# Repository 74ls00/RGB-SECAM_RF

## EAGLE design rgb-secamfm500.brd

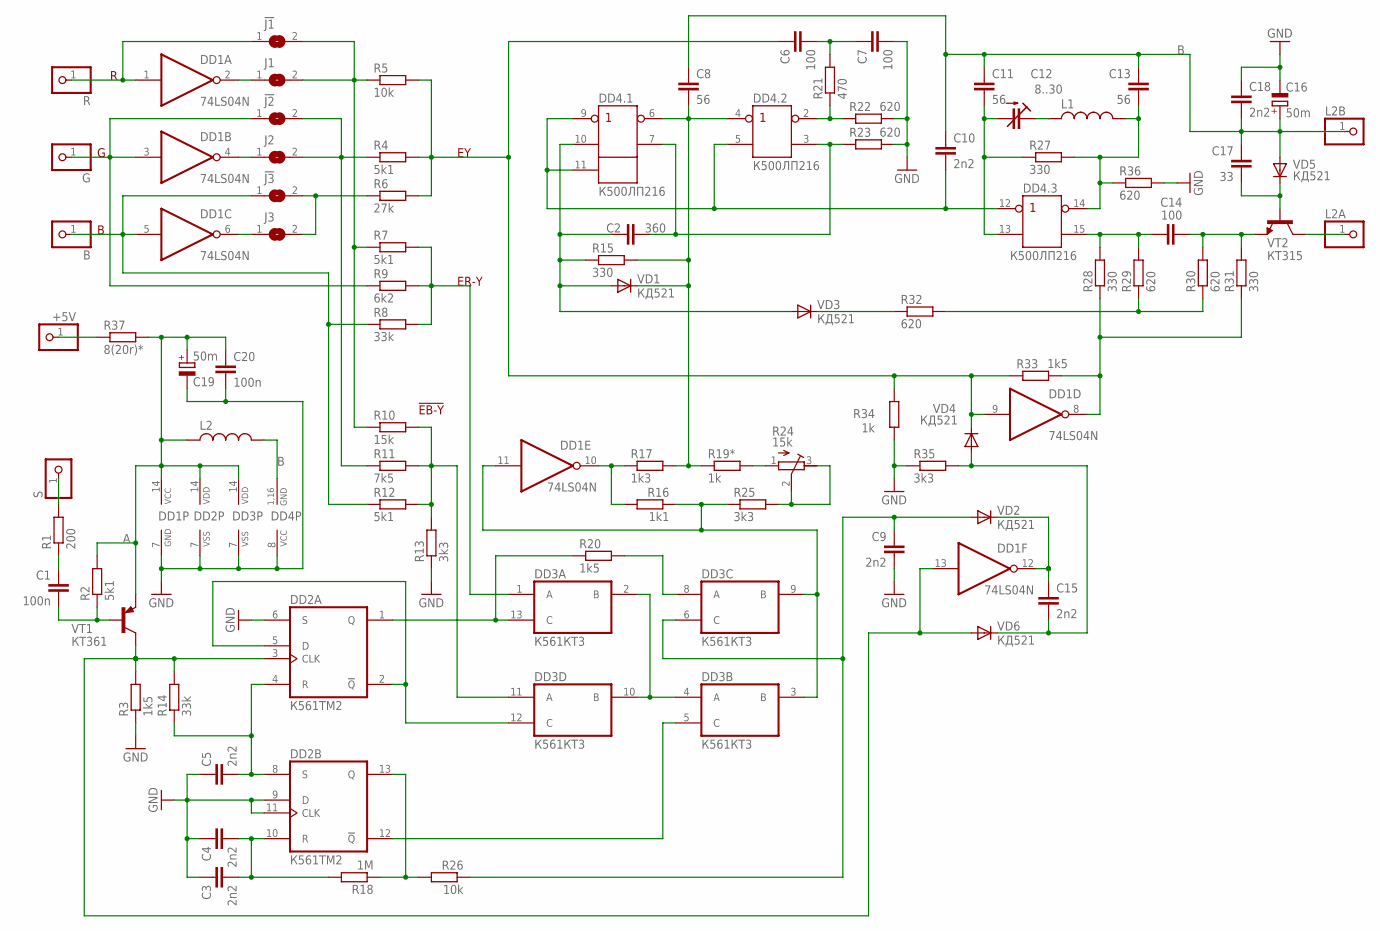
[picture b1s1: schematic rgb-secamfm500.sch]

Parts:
!J1, !J2, !J3: SJ
+5V: PINHD-1X1; 1X01
B: PINHD-1X1; 1X01
C1: 100n; C025-025X050
C2: 360; C0805K
C3, C4: 2n2; C0805
C5, C9, C10, C15, C18: 2n2; C0805K
C6, C7, C14: 100; C0805K
C8, C11, C13: 56; C0805K
C12: 8..30; CTRIM808-1
C16, C19: 50m; E2,5-6
C17: 33; C0805K
C20: 100n; C0805K
DD1: 74LS04N; DIL14
DD2: К561ТМ2; DIL14
DD3: К561КТ3; DIL14
DD4: К500ЛП216; DIL16B
G: PINHD-1X1; 1X01
J1, J2, J3: SJ
L1: L1
L2: L-US0204/5; 0204/5
L2A, L2B: PINHD-1X1; 1X01
R: PINHD-1X1; 1X01
R1: 200; M0805
R2, R4, R7, R12: 5k1; M0805
R3, R33: 1k5; M0805
R5, R26: 10k; M0805
R6: 27k; M0805
R8, R14: 33k; M0805
R9: 6k2; M0805
R10: 15k; M0805
R11: 7k5; M0805
R13, R25, R35: 3k3; M0805
R15: 330; 0207/12
R16: 1k1; M0805
R17: 1k3; M0805
R18: 1M; M0805
R19*, R34: 1k; M0805
R20: 1k5; 0207/12
R21: 470; M0805
R22, R23, R29, R30, R32, R36: 620; M0805
R24: 15k; RTRIM3296W
R27, R28, R31: 330; M0805
R37: 8(20r)*; R1210
S: PINHD-1X1; 1X01
VD1, VD2, VD3, VD4, VD5, VD6: КД521; D-7.5
VT1: КТ361; TO92
VT2: КТ315; TO92

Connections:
A: C19.+, C20.1, DD1.14 (VCC), DD2.14 (VDD), DD3.14 (VDD), L2.1, R2.2, R37.2, VT1.1 (E)
B: C8.1, C10.1, C11.1, C13.1, C16.+, C17.1, C18.2, DD4.1 (GND), DD4.16 (GND), L2.2, L2B.1, VD5.A
GND: C3.1, C4.1, C5.1, C7.2, C9.2, C16.-, C18.1, C19.-, C20.2, DD1.7 (GND), DD2.6 (S), DD2.7 (VSS), DD2.9 (D), DD2.11 (CLK), DD3.7 (VSS), DD4.8 (VCC), R3.1, R13.1, R22.2, R23.2, R34.1, R35.1, R36.2
unnamed: DD2.13 (Q), R18.1, R26.2
unnamed: R32.1, VD3.C
unnamed: C6.1, DD1.9 (I), R4.2, R5.2, R6.2, R33.1, R34.2, VD4.C
unnamed: DD3.1 (A), R7.2, R8.2, R9.2
unnamed: DD3.11 (A), R10.2, R11.2, R12.2, R13.2
unnamed: !J1.1, DD1.1 (I), R.1
unnamed: !J1.2, J1.2, R5.1, R7.1, R10.1
unnamed: !J2.2, J2.2, R4.1, R11.1
unnamed: !J2.1, DD1.3 (I), G.1, R9.1
unnamed: DD1.6 (O), J3.1
unnamed: !J3.1, B.1, DD1.5 (I), R8.1, R12.1
unnamed: DD1.2 (O), J1.1
unnamed: DD3.2 (B), DD3.4 (A), DD3.10 (B)
unnamed: DD1.11 (I), DD3.3 (B), DD3.9 (B), R16.1, R25.1
unnamed: DD1.4 (O), J2.1
unnamed: !J3.2, J3.2, R6.1
unnamed: DD2.2 (!Q), DD2.5 (D), DD3.12 (C)
unnamed: C5.2, DD2.4 (R), DD2.8 (S), R14.1
unnamed: DD1.13 (I), DD2.3 (CLK), R3.2, R14.2, VD6.A, VT1.2 (C)
unnamed: DD2.1 (Q), DD3.13 (C), R20.1
unnamed: C1.2, R2.1, VT1.3 (B)
unnamed: R1.2, S.1
unnamed: C1.1, R1.1
unnamed: +5V.1, R37.1
unnamed: C3.2, C4.2, DD2.10 (R), R18.2
unnamed: DD2.12 (!Q), DD3.5 (C)
unnamed: DD1.10 (O), R16.2, R17.1
unnamed: C8.2, DD4.4 (!IN), DD4.6 (!OUT), R15.2, R17.2, R19*.1, VD1.C
unnamed: C9.1, DD3.6 (C), R26.1, VD2.A
unnamed: DD3.8 (A), R20.2
unnamed: C15.1, DD1.12 (O), VD2.C
unnamed: R24.2 (S), R24.3 (E), R25.2
unnamed: C10.2, DD4.5 (IN), DD4.9 (!IN), DD4.11 (V), DD4.12 (!IN)
unnamed: C11.2, C12.2 (A), DD4.13 (IN), R27.1
unnamed: R19*.2, R24.1 (A)
unnamed: C2.2, DD4.3 (OUT), DD4.7 (OUT), R23.1
unnamed: C2.1, DD4.10 (IN), R15.1, VD1.A, VD3.A
unnamed: DD4.2 (!OUT), R21.1, R22.1
unnamed: C6.2, C7.1, R21.2
unnamed: C13.2, DD4.14 (!OUT), L1.P$2 (2), R27.2, R36.1
unnamed: C12.1 (E), L1.P$1 (1)
unnamed: C17.2, VD5.C, VT2.3 (B)
unnamed: C14.1, DD4.15 (OUT), R28.2, R29.2
unnamed: C14.2, R30.2, R31.2, VT2.1 (E)
unnamed: R29.1, R30.1, R32.2
unnamed: DD1.8 (O), R28.1, R31.1, R33.2
unnamed: L2A.1, VT2.2 (C)
unnamed: C15.2, R35.2, VD4.A, VD6.C

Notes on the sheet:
ER-Y
!EB-Y

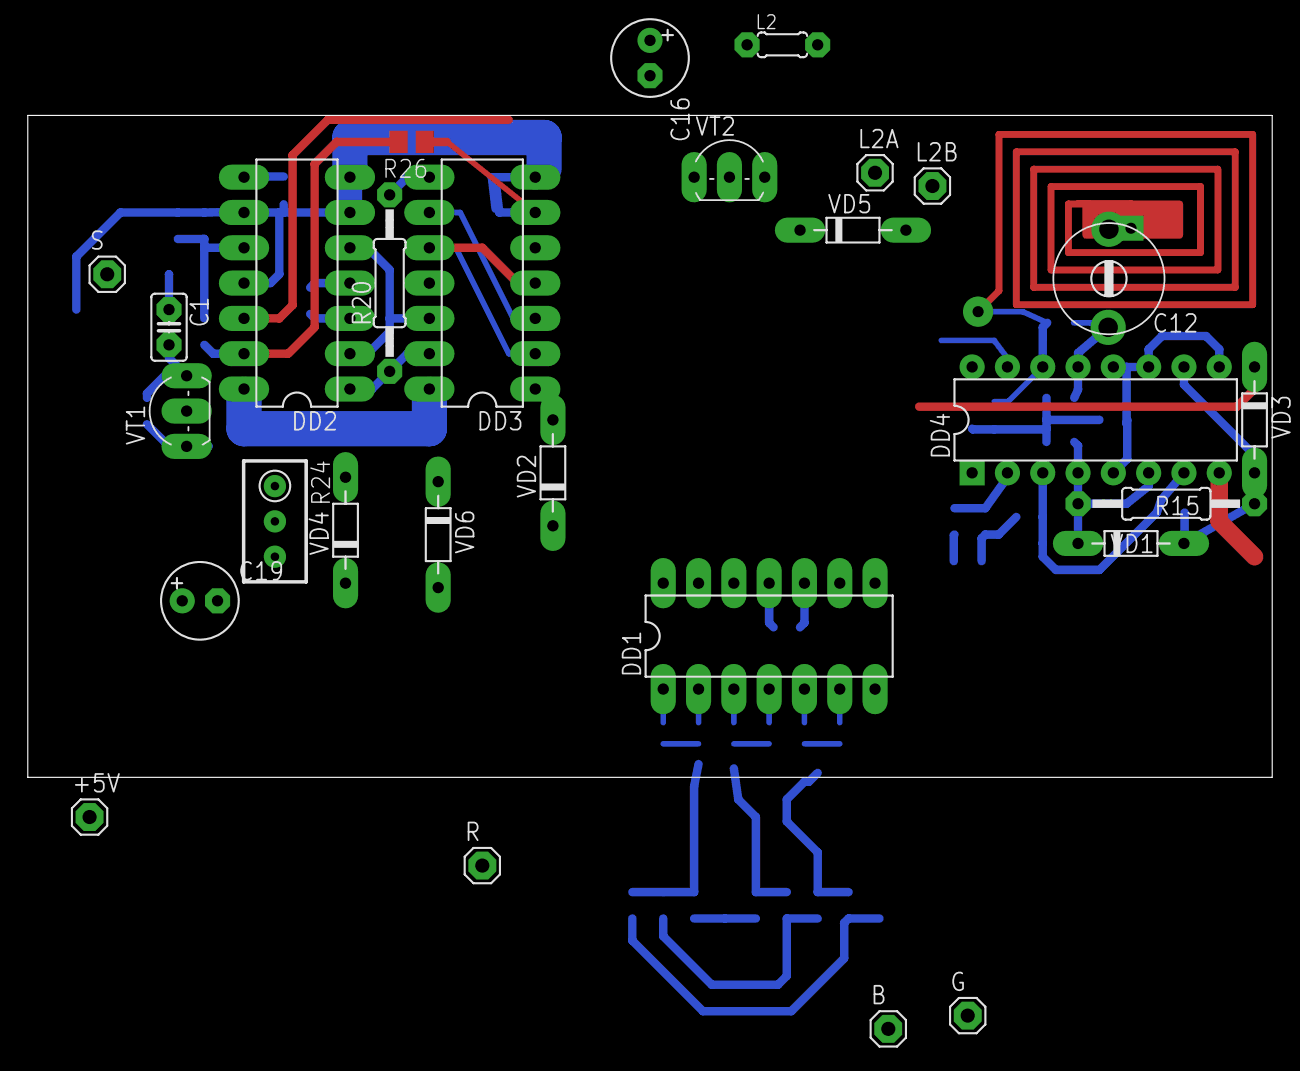
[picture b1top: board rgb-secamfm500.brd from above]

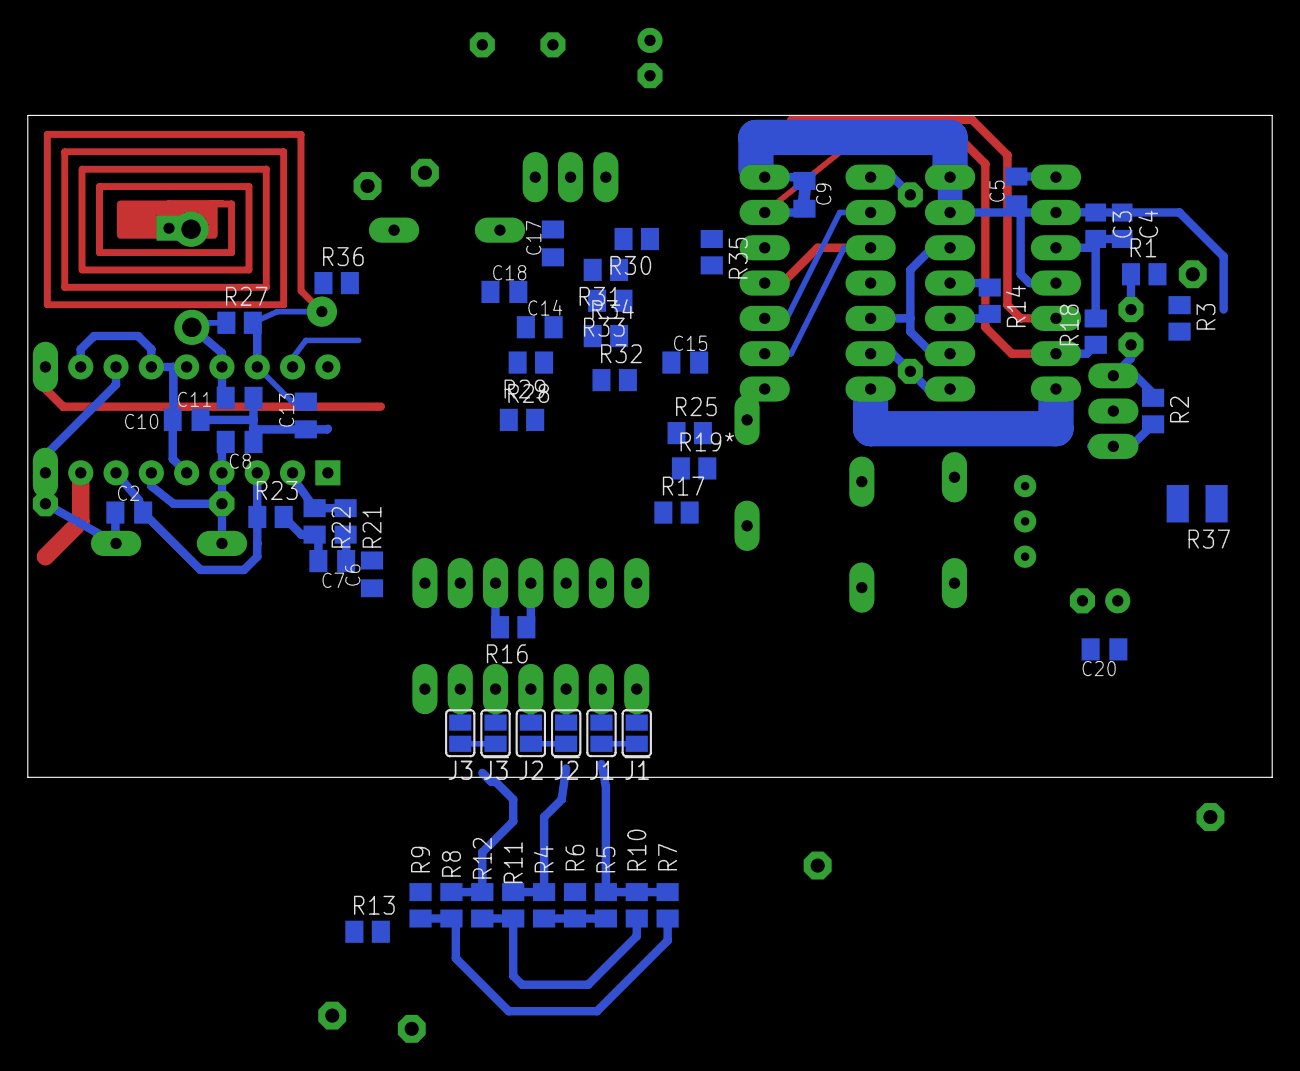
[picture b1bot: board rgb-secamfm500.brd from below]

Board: 2 copper layers, 89.5 x 47.6 mm, 84 parts (55 on the bottom side), 51 nets.
